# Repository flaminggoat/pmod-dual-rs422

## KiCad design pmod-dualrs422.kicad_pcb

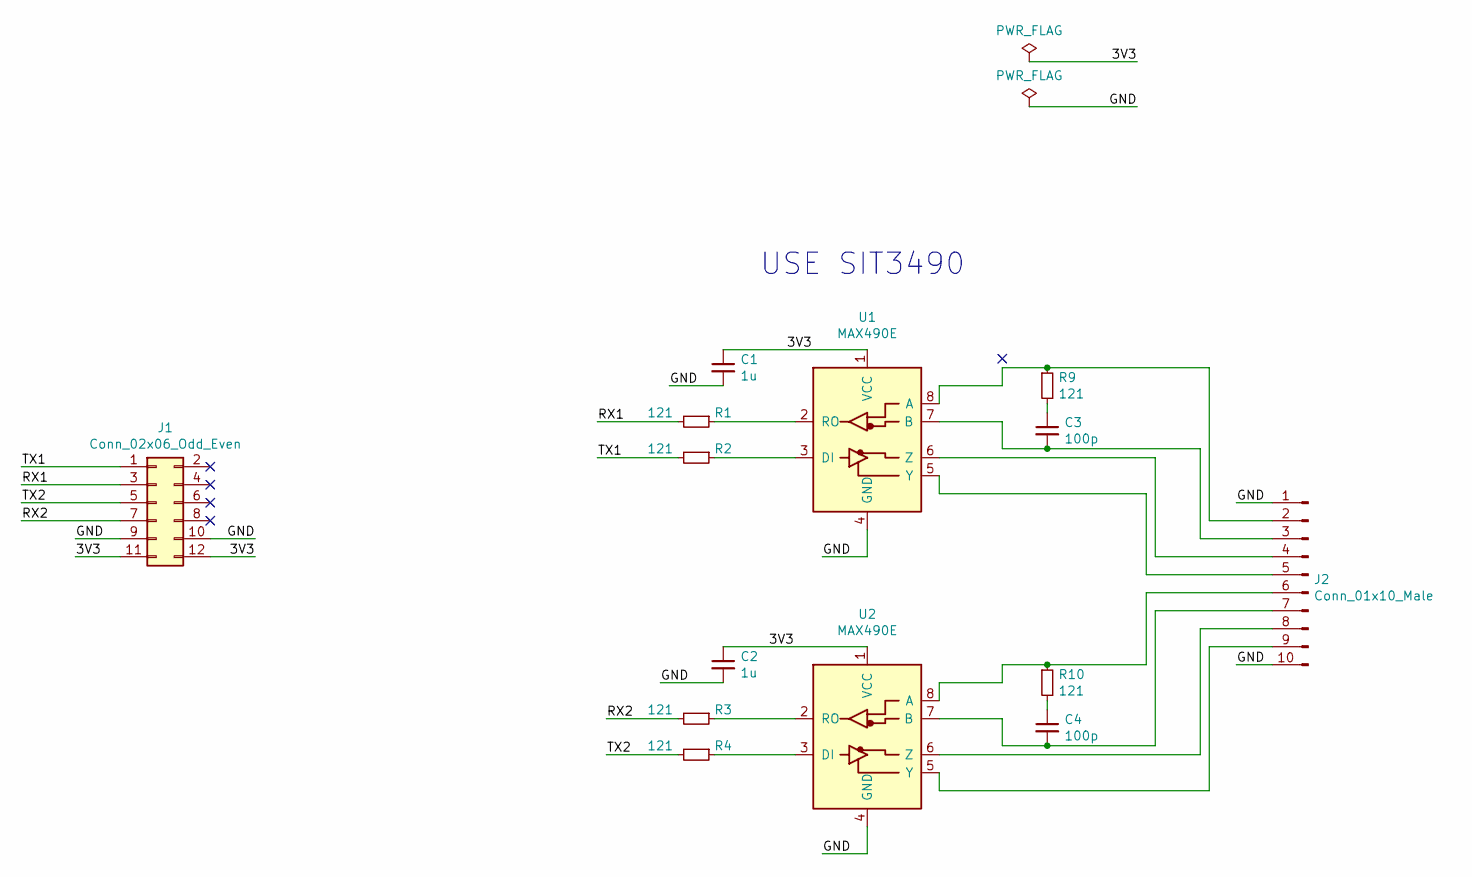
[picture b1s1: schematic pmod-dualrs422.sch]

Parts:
C1, C2: 1u; C_0805_2012Metric
C3, C4: 100p; C_0805_2012Metric
J1: Conn_02x06_Odd_Even; PinHeader_2x06_P2.54mm_Vertical
J2: Conn_01x10_Male; PinHeader_1x10_P2.54mm_Horizontal
R1, R2, R3, R4, R9, R10: 121; R_0805_2012Metric
U1, U2: MAX490E; SOIC-8_3.9x4.9mm_P1.27mm

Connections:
/3V3: C1.1, C2.1, J1.11, J1.12, U1.1 (VCC), U2.1 (VCC)
/GND: C1.2, C2.2, J1.9, J1.10, J2.1, J2.10, U1.4 (GND), U2.4 (GND)
/RX1: J1.3, R1.2
/RX2: J1.7, R3.2
/TX1: J1.1, R2.2
/TX2: J1.5, R4.2
unnamed: C3.1, R9.2
unnamed: C3.2, J2.3, U1.7 (B)
unnamed: C4.1, R10.2
unnamed: C4.2, J2.7, U2.7 (B)
unnamed: J2.2, R9.1, U1.8 (A)
unnamed: J2.4, U1.6 (Z)
unnamed: J2.5, U1.5 (Y)
unnamed: J2.6, R10.1, U2.8 (A)
unnamed: J2.8, U2.6 (Z)
unnamed: J2.9, U2.5 (Y)
unnamed: R1.1, U1.2 (RO)
unnamed: R2.1, U1.3 (DI)
unnamed: R3.1, U2.2 (RO)
unnamed: R4.1, U2.3 (DI)

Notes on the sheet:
USE SIT3490

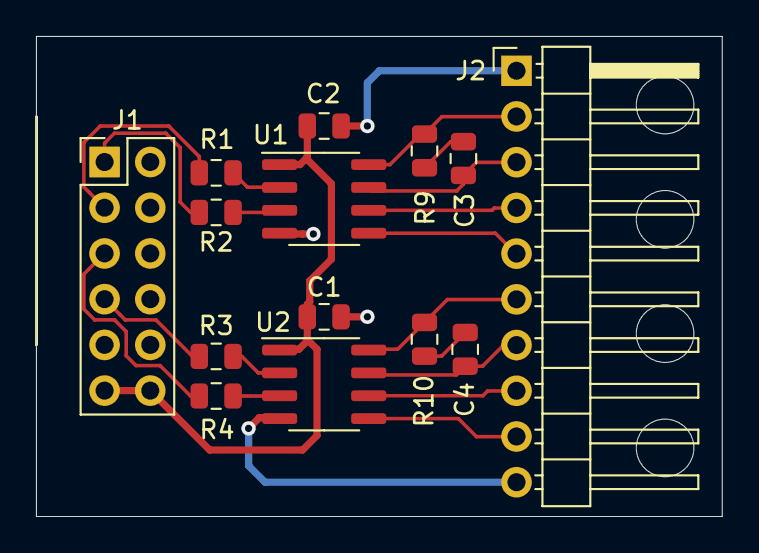
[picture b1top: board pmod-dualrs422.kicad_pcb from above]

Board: 2 copper layers, 38.1 x 26.7 mm, 14 parts (0 on the bottom side), 20 nets.

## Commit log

2020-02-12 Initial
2020-02-12 Added Documentation/pmod-dualrs422.pdf
